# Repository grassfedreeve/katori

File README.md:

# katori
30-key wireless topre/ec hummingbird keyboard based on the [rufous](https://github.com/jcmkk3/trochilidae) & [topreviung](https://gitlab.com/lpgalaxy/topreviung) 
---- 
named after katori senkō mosquito coils that inspired the original conical spring design for topre switches, as well as katori's translation to bird as homage to the hummingbird.

## Status
Revision 1 has been built and tested. Had design error fixed in r2 but yet to be officially ordered

## Manufacturing

Can be hand soldered or ordered assembled using assembly files

Currently setup to use a 1.2mm aluminum single layer pcb as the plate

- [PCB production files](./production/)
- [Plate files](./plate/)
- [Case files](./case)

## Parts needed
- 1 pcb
- 1 plate
- 1 case
- 1 seeed xiao compatible controller
- 30 1u EC housing + slider
- 30 Rubber domes
- 30 Conical springs
- 26 [m1.6 5mm full thread standoffs](https://www.aliexpress.com/item/1005004397115309.html) 
- 1 [3x6x5 tht reset switch](https://www.aliexpress.com/store/1103739763)
- 26 m1.6 3mm screws
- 6 m3 3mm screws

## BOM
- 1 PCM12SMTR - power switch
- 7 SMTSO3020MTJ - SMD solder nut
- 2 TSSOP-16 multiplexers
- 1 0603 1k resistor
- 13 0603 100k resistors
- 3 0603 100n capacitors
- 1 0603 220pF capacitor

**Optional**
- Silencing rings
- [450mah 601148 battery](https://www.aliexpress.com/item/32844347206.html)
- 1 PCM12SMTR - power switch

#### PCB Renders

## Inspiration & Thanks
- jcmkk3's [rufous](https://github.com/jcmkk3/trochilidae#rufous) hummingbird variation, of which I used the Ergogen config and splay etc.
- pete johanson for his incredible help during the project and his [topreviung](https://gitlab.com/lpgalaxy/topreviung) keyboard, which was the basis of the schematic and entire EC portions.
- PJE66's original [hummingbird](https://github.com/PJE66/hummingbird) keyboard

## Acknowledgements 
Thank you to [PCBWay](https://www.pcbway.com/) for sponsoring this project!

You can find and order the parts for this project on PCBWay using these links:

[pcb](https://www.pcbway.com/project/shareproject/Katori_30_key_wireless_topre_ec_hummingbird_keyboard_7163f60f.html)
[plate](https://www.pcbway.com/project/shareproject/Katori_Plate_a08691e4.html)

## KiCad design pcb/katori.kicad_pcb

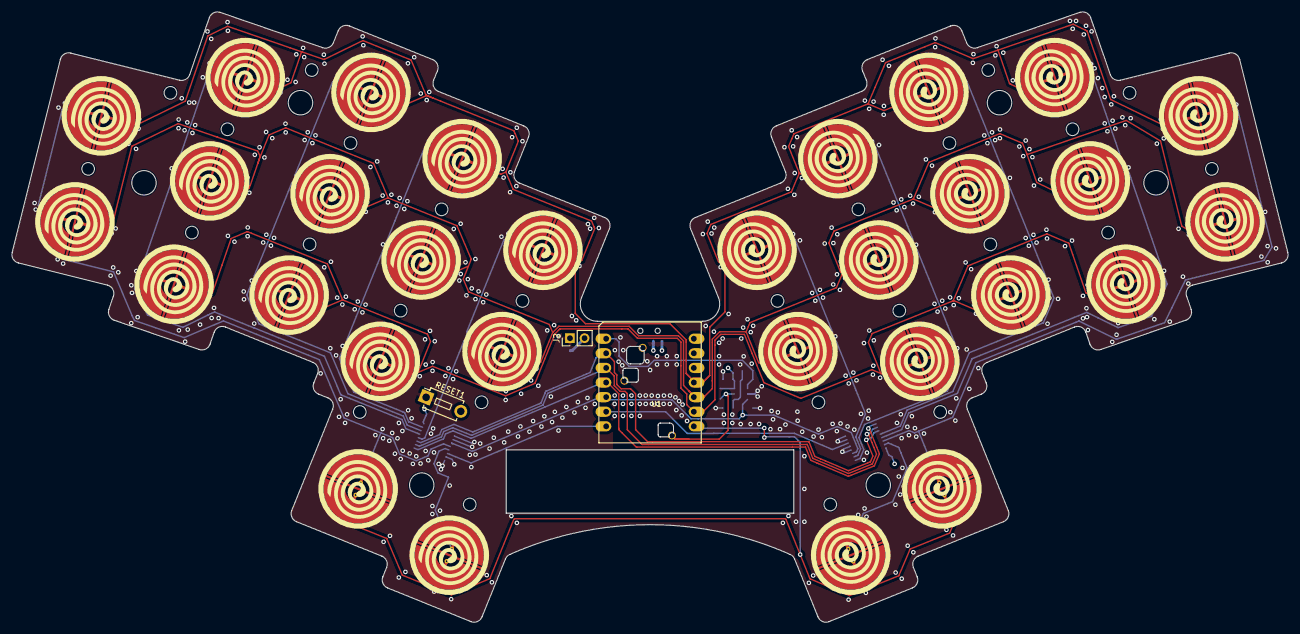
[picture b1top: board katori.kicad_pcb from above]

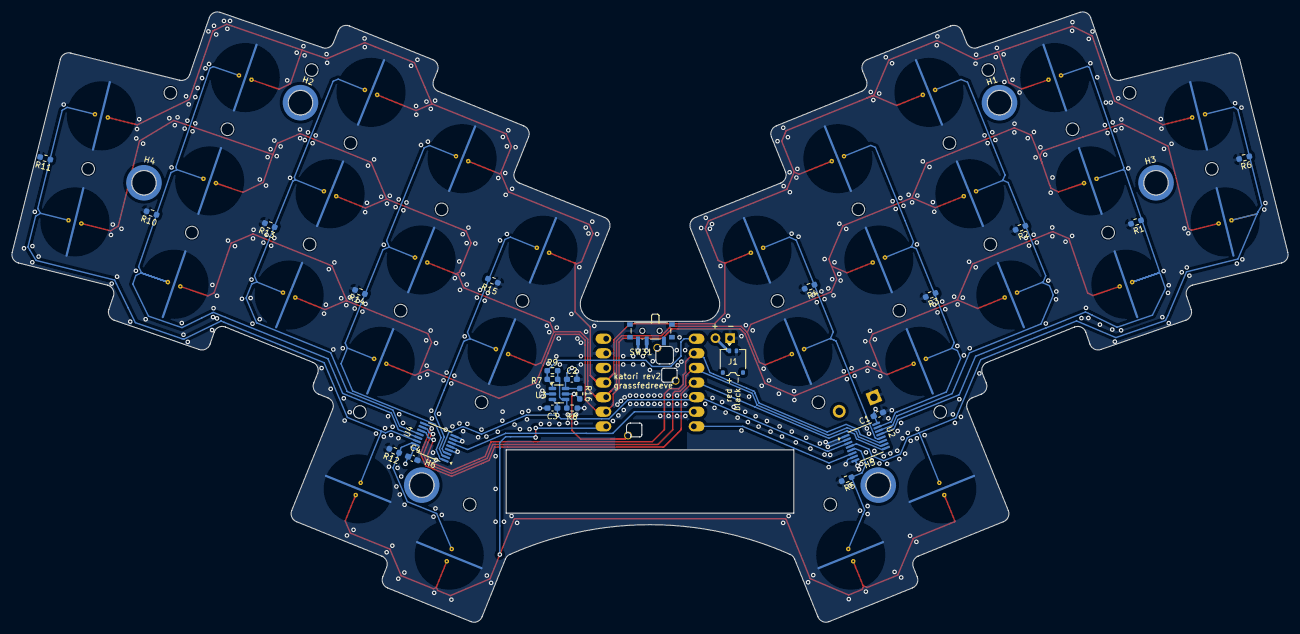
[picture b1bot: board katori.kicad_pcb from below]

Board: 4 copper layers, 221.8 x 106.0 mm, 98 parts (31 on the bottom side), 30 nets.

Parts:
BUMP1, BUMP2, BUMP3, BUMP4, BUMP5, BUMP6, BUMP7, BUMP8: MountingHole; Bumpon
C1, C2, C4: 100n; C_0603_1608Metric_Pad1.08x0.95mm_HandSolder
C3: 220pF; C_0603_1608Metric_Pad1.08x0.95mm_HandSolder
H1, H2, H3, H4, H5, H6: MountingHole; MountingHole_3mm_Pad_NonPTH_TopOnly
J1: JST ACH; JST_ACH_BM02B-ACHSS-GAN-ETF_1x02-1MP_P1.20mm_Vertical
J2: Solder; PinHeader_1x02_P2.54mm_Vertical
PH1, PH2, PH3, PH4, PH5, PH6, PH7, PH8, PH9, PH10, PH11, PH12, PH13, PH14, PH15, PH16, PH17, PH18, PH19, PH20, PH21, PH22, PH23, PH24, PH27, PH28: MountingHole; MountingHole_2.2mm_M2
R1, R2, R3, R4, R5, R6, R7, R10, R11, R12, R13, R14, R15: 100k; R_0603_1608Metric_Pad0.98x0.95mm_HandSolder
R8: 1k; R_0603_1608Metric_Pad0.98x0.95mm_HandSolder
R9: DNP; R_0603_1608Metric_Pad0.98x0.95mm_HandSolder
R16: 1M; R_0603_1608Metric_Pad0.98x0.95mm_HandSolder
RESET1: SW_PUSH; SW_PUSH_1P1T_6x3.5mm_H5.0_APEM_MJTP1250
SW1, SW2, SW3, SW4, SW5, SW6, SW7, SW8, SW9, SW10, SW11, SW12, SW13, SW14, SW15, SW16, SW17, SW18, SW19, SW20, SW21, SW22, SW23, SW24, SW25, SW26: EC_SW; katori_pad_1U_90deg
SW27, SW28, SW29, SW30: EC_SW; katori_pad_1U
SW31: POWER; SW_SPDT_PCM12
U1: SeeeduinoXIAO_Hybrid; xiao-ble-tht-cutout-topre-no-reset-outline
U2, U4: 74HC4051; TSSOP-16_4.4x5mm_P0.65mm
U3: OPA357AIDBVR; SOT-23-6

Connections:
+3V3: C1.2, C2.2, C4.2, R16.1, U1.12 (3V3), U2.16 (VCC), U3.6 (V+), U4.16 (VCC)
+BATT: SW31.3 (C), U1.16 (BAT+)
/BATT_RAW: J1.1, J2.2, SW31.2 (B)
/NRST: RESET1.2, U1.15 (RESET)
ADC: R7.1, R9.1, U1.1 (PA02_A0_D0), U3.1
ADC_ENABLE: R16.2, U1.17 (NFC1), U3.5 (ENABLE)
AMUX_SEL_0: U1.2 (PA4_A1_D1), U2.11 (S0), U4.11 (S0)
AMUX_SEL_1: U1.3 (PA10_A2_D2), U2.10 (S1), U4.10 (S1)
AMUX_SEL_2: U1.4 (PA11_A3_D3), U2.9 (S2), U4.9 (S2)
APLEX_EN0: U1.7 (PB08_A6_D6_TX), U2.6 (~E)
APLEX_EN1: U1.6 (PA9_A5_D5_SCL), U4.6 (~E)
APLEX_OUT: C3.1, U1.5 (PA8_A4_D4_SDA), U2.3 (A), U3.3 (+), U4.3 (A)
COL0: R6.1, SW1.1, SW11.1, SW27.2, U2.4 (A7)
COL1: R1.1, SW2.1, SW12.1, SW21.1, U2.13 (A0)
COL2: R2.1, SW3.1, SW13.1, SW22.1, U2.14 (A1)
COL3: R3.1, SW4.1, SW14.1, SW23.1, U2.15 (A2)
COL4: R4.1, SW5.1, SW15.1, U2.12 (A3)
COL5: R15.1, SW6.1, SW16.1, U4.2 (A6)
COL6: R14.1, SW7.1, SW17.1, SW24.1, U4.1 (A4)
COL7: R13.1, SW8.1, SW18.1, SW25.1, U4.12 (A3)
COL8: R10.1, SW9.1, SW19.1, SW26.1, U4.13 (A0)
COL9: R11.1, SW10.1, SW20.1, SW30.1, U4.14 (A1)
COL10: R5.1, SW28.2, U2.5 (A5)
COL11: R12.1, SW29.1, U4.15 (A2)
GND: C1.1, C2.1, C3.2, C4.1, J1.2, J2.1, R1.2, R2.2, R3.2, R4.2, R5.2, R6.2, R8.2, R10.2, R11.2, R12.2, R13.2, R14.2, R15.2, RESET1.1, SW1.3 (SG), SW2.3 (SG), SW3.3 (SG), SW4.3 (SG), SW5.3 (SG), SW6.3 (SG), SW7.3 (SG), SW8.3 (SG), SW9.3 (SG), SW10.3 (SG), SW11.3 (SG), SW12.3 (SG), SW13.3 (SG), SW14.3 (SG), SW15.3 (SG), SW16.3 (SG), SW17.3 (SG), SW18.3 (SG), SW19.3 (SG), SW20.3 (SG), SW21.3 (SG), SW22.3 (SG), SW23.3 (SG), SW24.3 (SG), SW25.3 (SG), SW26.3 (SG), SW27.3 (SG), SW28.3 (SG), SW29.3 (SG), SW30.3 (SG), U1.13 (GND), U2.1 (A4), U2.2 (A6), U2.7 (VEE), U2.8 (GND), U3.2 (V-), U4.4 (A7), U4.5 (A5), U4.7 (VEE), U4.8 (GND)
unnamed: R7.2, R8.1, R9.2, U3.4 (-)
ROW0: SW1.2, SW2.2, SW3.2, SW4.2, SW5.2, SW6.2, SW7.2, SW8.2, SW9.2, SW10.2, U1.11 (PA6_A10_D10_MOSI)
ROW1: SW11.2, SW12.2, SW13.2, SW14.2, SW15.2, SW16.2, SW17.2, SW18.2, SW19.2, SW20.2, U1.10 (PA5_A9_D9_MISO)
ROW2: SW21.2, SW22.2, SW23.2, SW24.2, SW25.2, SW26.2, U1.9 (PA7_A8_D8_SCK)
ROW3: SW27.1, SW28.1, SW29.2, SW30.2, U1.8 (PB09_A7_D7_RX)

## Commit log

2024-11-30 initial commit after cleanup
2024-12-21 update bom
2025-03-08 revision 2 and readme updates
2025-03-08 readme
